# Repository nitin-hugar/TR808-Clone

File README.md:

# TR808-Clone
A modified schematic and PCB made on EAGLE for a clone of the Roland TR808 analog kick and snare synthesizer

## Schematic:

## PCB Layout:

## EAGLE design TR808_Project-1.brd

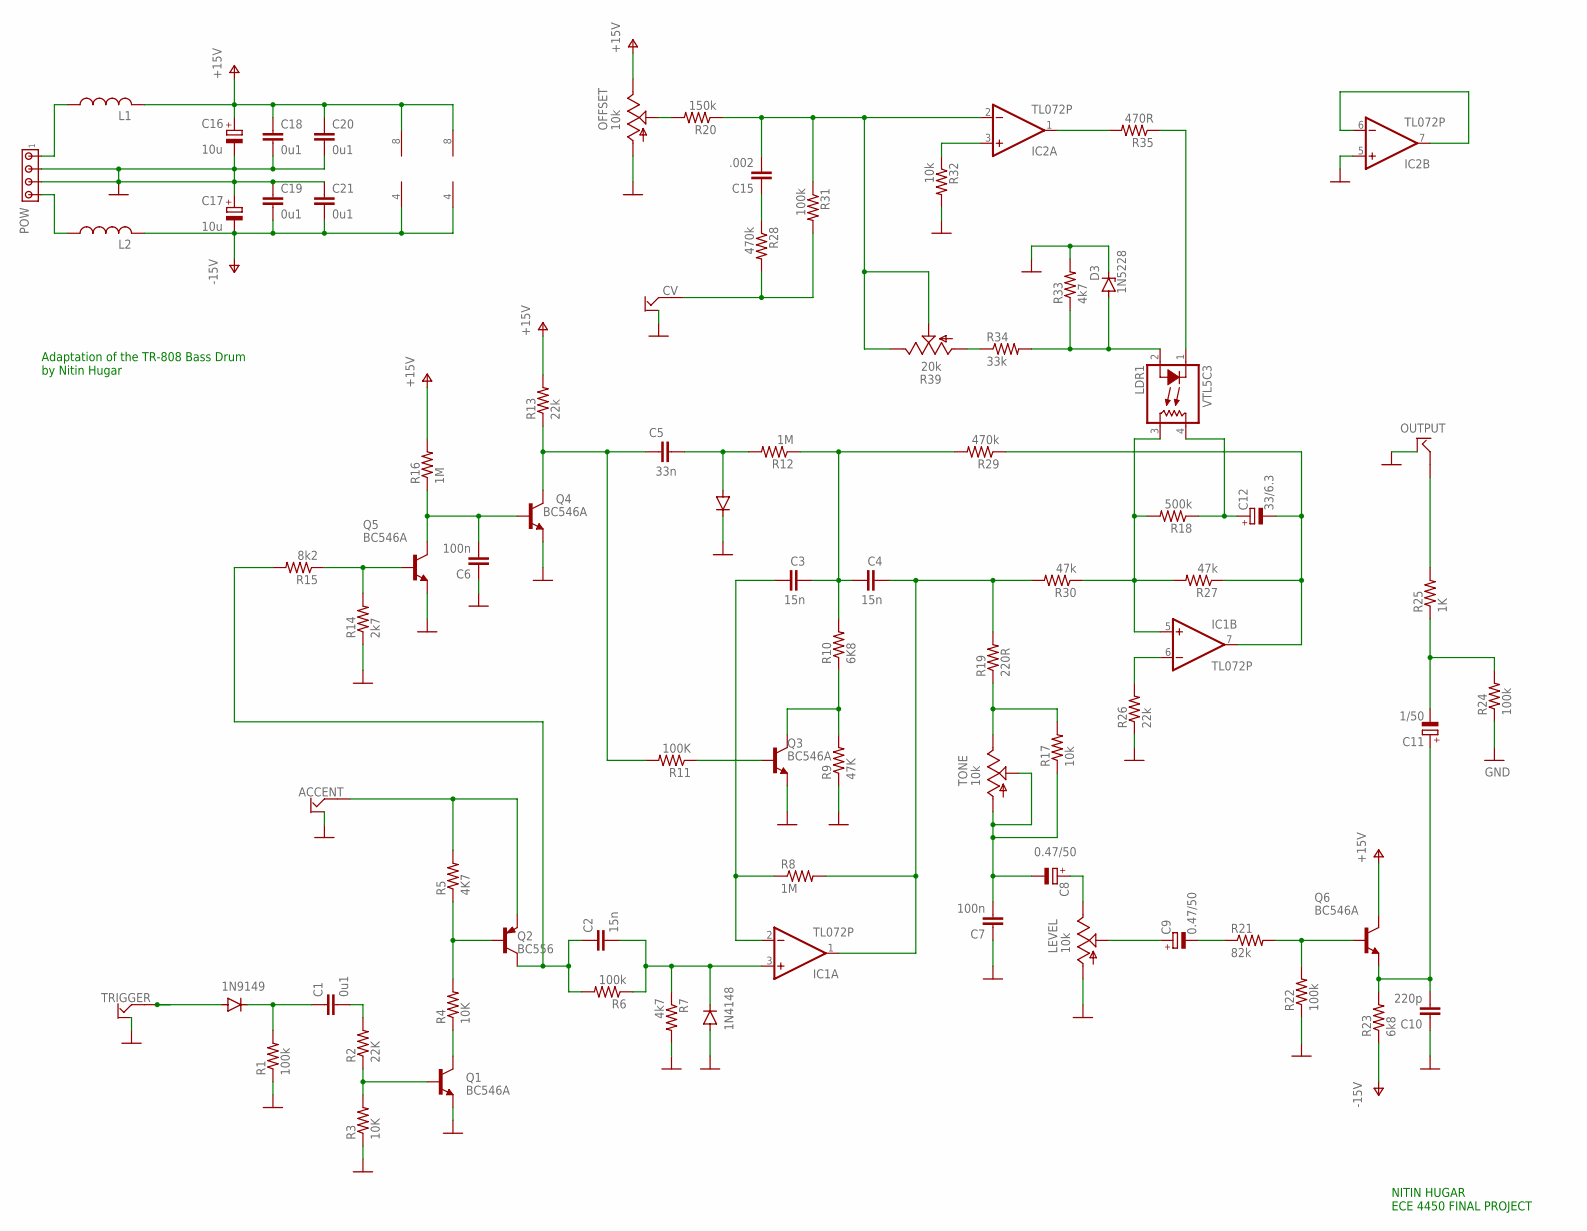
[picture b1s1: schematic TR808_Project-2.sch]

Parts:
1N4148: 1N4148; DO35-10
ACCENT: OFFBOARD2JACKALT_AARON; OFFBOARD2JACKALT
C1, C18, C19, C20, C21: 0u1; C050-025X075
C2, C3, C4: 15n; C050-025X075
C5: 33n; C050-025X075
C6, C7: 100n; C050-025X075
C8, C9: 0.47/50; E1,8-4
C10: 220p; C050-025X075
C11: 1/50; E1,8-4
C12: 33/6.3; E1,8-4
C15: .002; C050-025X075
C16, C17: 10u; E1,8-4
CV: OFFBOARD2JACKALT_AARON; OFFBOARD2JACKALT
D1: 1N9149; D-10
D2: 1N4148; DO35-10
D3: 1N5228; C1702-15
IC1, IC2: TL072P; DIL08
L1, L2: L-US0207/10; 0207/10
LDR1: VTL5C3; VTL5C
LEVEL: 10k; B64Y
OFFSET: 10k; B64Y
OUTPUT: OFFBOARD2JACKALT_AARON; OFFBOARD2JACKALT
POW: MTA04-156; 1X4MTA
Q1, Q3, Q4, Q5, Q6: BC546A; TO92-EBC
Q2: BC556; TO92-EBC
R1, R6, R22, R24, R31: 100k; 0207/10
R2: 22K; 0207/10
R3, R4: 10K; 0207/10
R5: 4K7; 0207/10
R7, R33: 4k7; 0207/10
R8, R12, R16: 1M; 0207/10
R9: 47K; 0207/10
R10: 6K8; 0207/10
R11: 100K; 0207/10
R13, R26: 22k; 0207/10
R14: 2k7; 0207/10
R15: 8k2; 0207/10
R17, R32: 10k; 0207/10
R18: 500k; 0207/10
R19: 220R; 0207/10
R20: 150k; 0207/10
R21: 82k; 0207/10
R23: 6k8; 0207/10
R25: 1K; 0207/10
R27, R30: 47k; 0207/10
R28, R29: 470k; 0207/10
R34: 33k; 0207/10
R35: 470R; 0207/10
R39: 20k; B64Y
TONE: 10k; B64Y
TRIGGER: OFFBOARD2JACKALT_AARON; OFFBOARD2JACKALT

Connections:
D1: C1.1, D1.C, R1.2
GND: 1N4148.A, ACCENT.GND, C6.1, C7.1, C10.1, C16.-, C17.+, C18.2, C19.1, C20.2, C21.1, CV.GND, D2.C, D3.C, IC2.5 (+IN), LEVEL.A, OFFSET.A, OUTPUT.GND, POW.2, POW.3, Q1.E, Q3.E, Q4.E, Q5.E, R1.1, R3.1, R7.2, R9.1, R14.1, R22.1, R24.1, R26.1, R32.2, R33.2, TRIGGER.GND
unnamed: C12.+, LDR1.4 (L2), R18.1
unnamed: C1.2, R2.2
unnamed: Q1.B, R2.1, R3.2
unnamed: Q1.C, R4.1
unnamed: Q2.B, R4.2, R5.1
unnamed: ACCENT.SIGNAL, Q2.E, R5.2
unnamed: D1.A, TRIGGER.SIGNAL
unnamed: C2.1, Q2.C, R6.2, R15.2
unnamed: 1N4148.C, C2.2, IC1.3 (+IN), R6.1, R7.1
unnamed: Q3.B, R11.1
unnamed: C4.2, IC1.1 (OUT), R8.2, R19.2, R30.2
unnamed: Q3.C, R9.2, R10.1
unnamed: C3.2, C4.1, R10.2, R12.1, R29.2
unnamed: C15.2, IC2.2 (-IN), R20.1, R31.1, R39.E, R39.S
unnamed: C5.2, D2.A, R12.2
unnamed: C5.1, Q4.C, R11.2, R13.1
unnamed: Q5.B, R14.2, R15.1
unnamed: C6.2, Q4.B, Q5.C, R16.1
unnamed: R17.2, R19.1, TONE.E
unnamed: C8.+, LEVEL.E
unnamed: C9.+, LEVEL.S
unnamed: C9.-, R21.1
unnamed: Q6.B, R21.2, R22.2
unnamed: C10.2, C11.+, Q6.E, R23.2
unnamed: C11.-, R24.2, R25.1
unnamed: OUTPUT.SIGNAL, R25.2
unnamed: IC1.6 (-IN), R26.2
unnamed: IC1.5 (+IN), LDR1.3 (L1), R18.2, R27.2, R30.1
unnamed: C12.-, IC1.7 (OUT), R27.1, R29.1
unnamed: C15.1, R28.1
unnamed: C7.2, C8.-, R17.1, TONE.A, TONE.S
unnamed: IC2.3 (+IN), R32.1
unnamed: OFFSET.S, R20.2
unnamed: IC2.1 (OUT), R35.2
unnamed: R34.1, R39.A
unnamed: IC2.6 (-IN), IC2.7 (OUT)
unnamed: LDR1.1 (C), R35.1
unnamed: D3.A, LDR1.2 (A), R33.1, R34.2
unnamed: CV.SIGNAL, R28.2, R31.2
unnamed: C3.1, IC1.2 (-IN), R8.1
unnamed: L1.1, POW.1
unnamed: L2.1, POW.4
V+: C16.+, C18.1, C20.1, IC1.8 (V+), IC2.8 (V+), L1.2, OFFSET.E, Q6.C, R13.2, R16.2
V-: C17.-, C19.2, C21.2, IC1.4 (V-), IC2.4 (V-), L2.2, R23.1

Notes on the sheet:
NITIN HUGAR ECE 4450 FINAL PROJECT
Adaptation of the TR-808 Bass Drum by Nitin Hugar

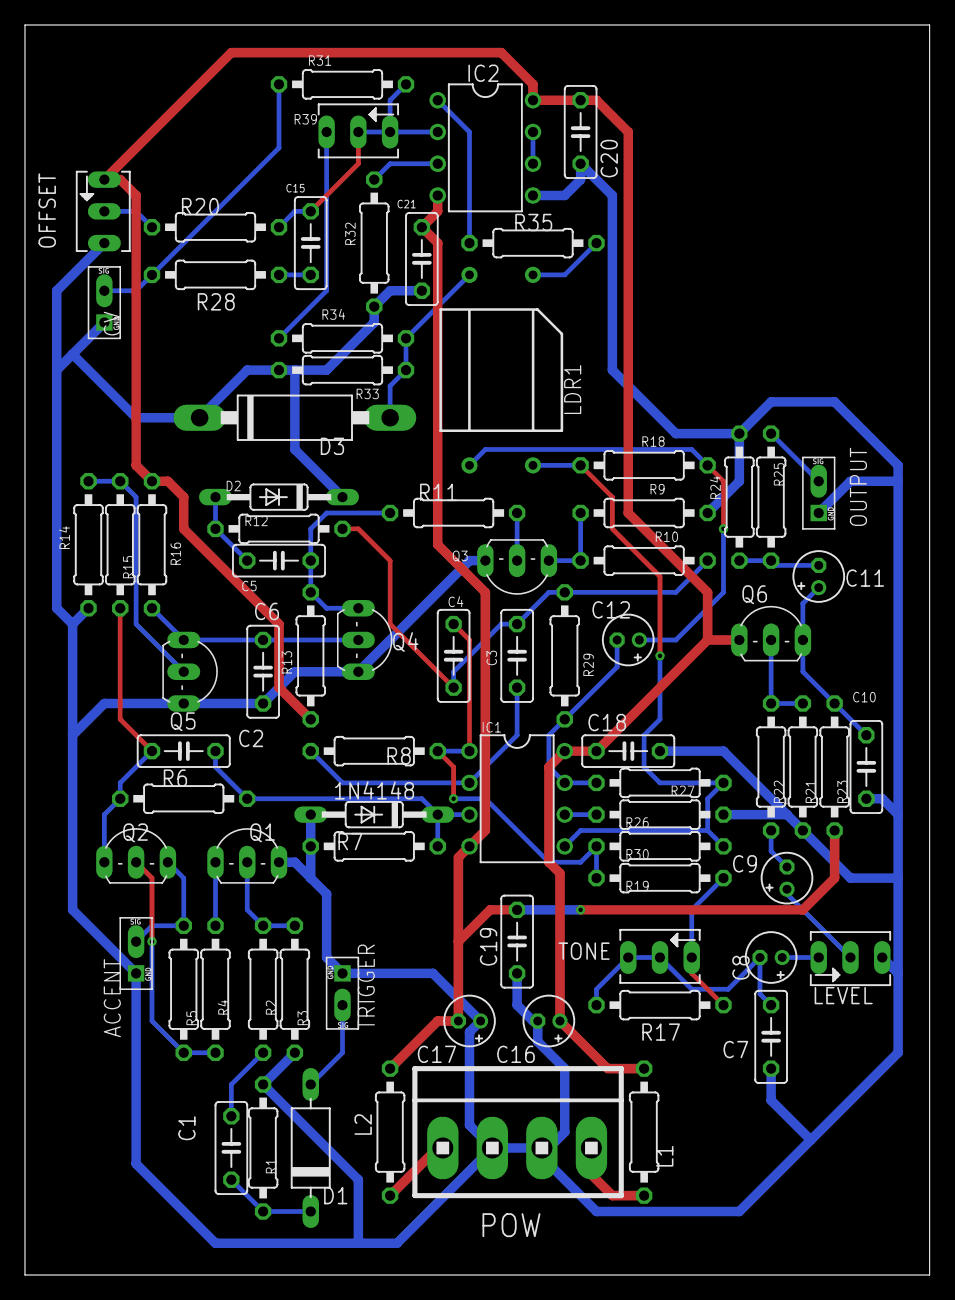
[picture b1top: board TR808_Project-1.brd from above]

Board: 2 copper layers, 72.4 x 100.0 mm, 78 parts (0 on the bottom side), 46 nets.
